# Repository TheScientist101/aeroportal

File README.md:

# Aeroportal

Aeroportal is a weather-centered home hub that is designed with simplicity at its core.

The dashboard is hosted at: https://aeroportal.urjith.dev/

# Features

- Weather information
- Time and date
- Alarms
- Broadcast audio messages

# Hardware

## PCB

The PCB is designed in KiCad which is in the `pcb` folder. The electronics consist of a Wemos C3 mini, a TFT display, an I2S amplifier, and a speaker. The PCB is designed to be powered by a USB-C cable connected a wall outlet.

|         Schematic         |         PCB         |
| :-----------------------: | :-----------------: |
|  |  |

- [x] I ran DRC in KiCad and have made sure there are 0 errors!

## Case

The case is designed in Openscad which is in the `cad` folder. To assemble, print the top and bottom parts of the case and assemble them as shown in `cad/assembled.scad`. Glue the holes in the top part to the bottom part to help keep the case together.

It's supposed to look like a lightning bolt, but it I've squeezed it a little due to sizing constraints.

# Software

## Website

The dashboard website is written in Next.js with the Next UI library for the UI components. The website is in the `website` folder. The website is hosted at: https://aeroportal.urjith.dev/.

## Firmware

The firmware is written in Circuitpython and is currently very rudamentary since I do not currently have the hardware to test it. The firmware is in the `firmware` folder. It _should_ be able to connect to the internet, display the weather information on the TFT display, and play scheduled alarms or broadcasted messages (using the API).

- [x] I remembered to exclude any personal information, including API Keys, WiFi passwords, etc

# BOM

Provided by dari // alex:

- 1x WeMos C3 Mini (as a cheaper replacement for the S2) WITHOUT FEMALE HEADERS
- 1x ST7735 1.8" LCD display WITHOUT FEMALE HEADERS. Male headers soldered!

I will be printing my case myself for the additional $10 in my grant.

- 1x Top Half of the Case
- 1x Bottom Half of the Case

I will be sourcing the following parts with my grant:

- 1x PCB from JLCPCB
  - $2 for 5x + $1.50 shipping
- 1x 2.5 Inch 4 Ohm, 3 Watt Speaker [(AliExpress)](https://www.aliexpress.us/item/2251832660654764.html)
  - $3.69 + $1.99 shipping
- 1x MAX98357A I2S Amplifier [(AliExpress)](https://www.aliexpress.us/item/3256805196806369.html)
  - $1.73
- 1x USB-C Cable [(AliExpress)](https://www.aliexpress.us/item/3256806318726664.html)
  - $3.21
- 1x 18 AWG Wire for Speaker [(AliExpress)](https://www.aliexpress.us/item/3256807019333756.html)
  - $8.66
  - Note, this price has been fluctuating a lot (it was around $5 earlier), so I may use a different link if it goes up too much.

Total before tax: $22.78
Total after tax: $24.66

I'll also be source the following parts myself since I already have them and would like to help Hack Club:

- 1x 10 Ohm Resistor

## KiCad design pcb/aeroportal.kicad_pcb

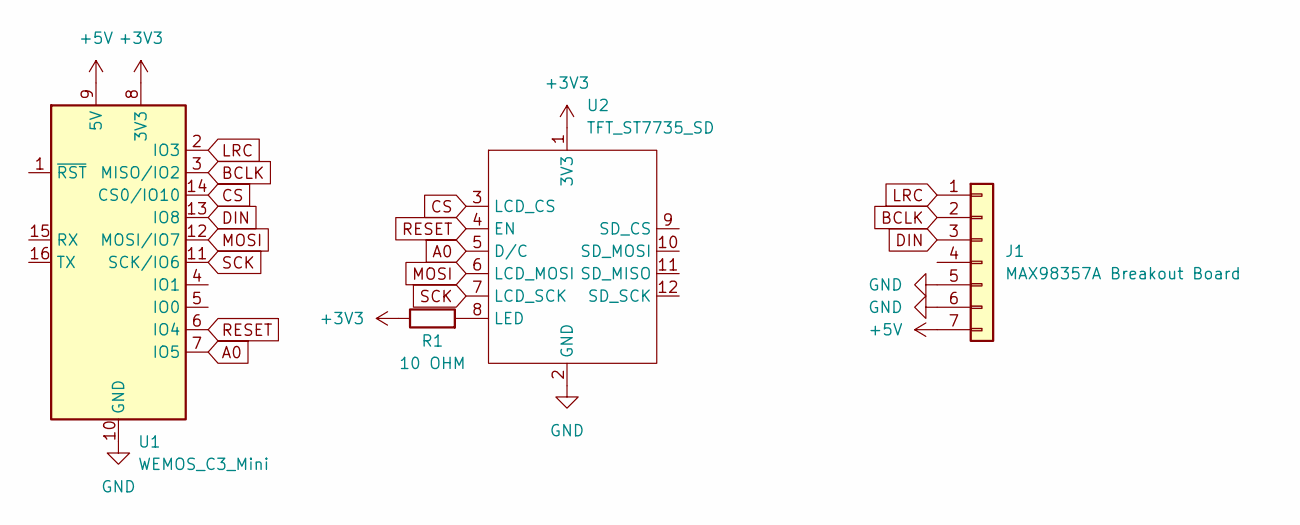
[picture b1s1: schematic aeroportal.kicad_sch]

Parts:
J1: MAX98357A Breakout Board; PinHeader_1x07_P2.54mm_Vertical
R1: 10 OHM; R_Axial_DIN0207_L6.3mm_D2.5mm_P10.16mm_Horizontal
U1: WEMOS_C3_Mini; WEMOS_D1_mini_light
U2: TFT_ST7735_SD

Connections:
+3V3: R1.1, U1.8 (3V3), U2.1 (3V3)
+5V: J1.7, U1.9 (5V)
A0: U1.7 (IO5), U2.5 (D/C)
BCLK: J1.2, U1.3 (MISO/IO2)
CS: U1.14 (CS0/IO10), U2.3 (LCD_CS)
DIN: J1.3, U1.13 (IO8)
GND: J1.5, J1.6, U1.10 (GND), U2.2 (GND)
LRC: J1.1, U1.2 (IO3)
MOSI: U1.12 (MOSI/IO7), U2.6 (LCD_MOSI)
unnamed: R1.2, U2.8 (LED)
RESET: U1.6 (IO4), U2.4 (EN)
SCK: U1.11 (SCK/IO6), U2.7 (LCD_SCK)

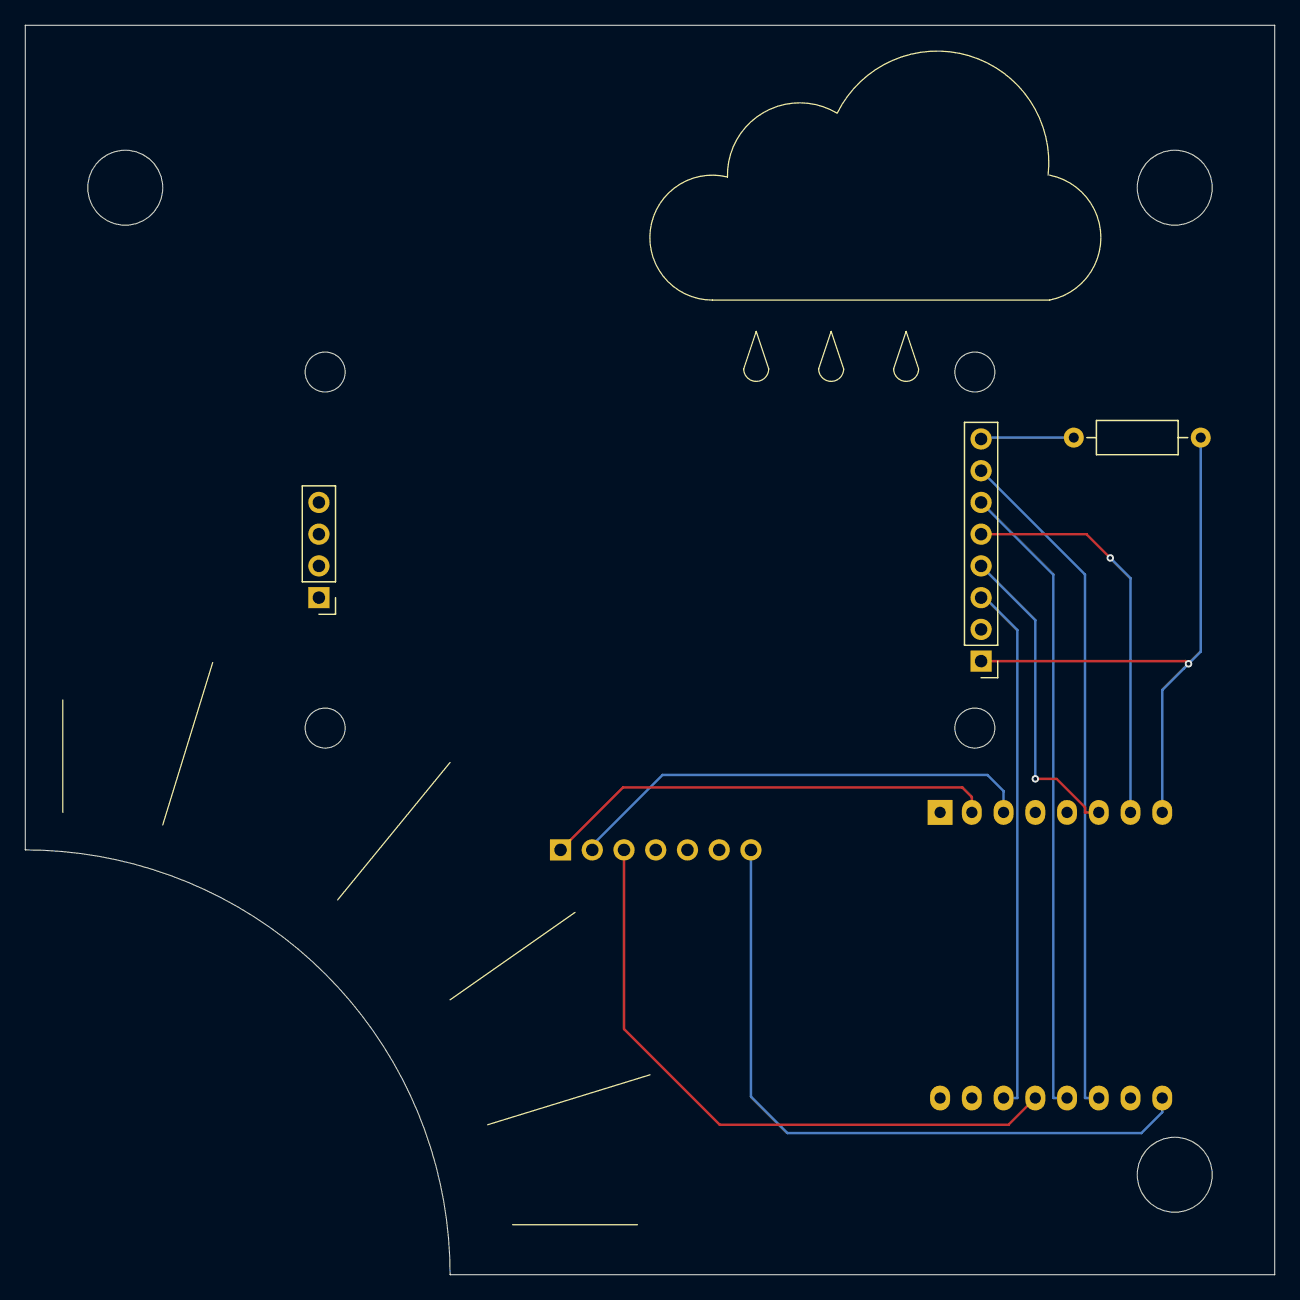
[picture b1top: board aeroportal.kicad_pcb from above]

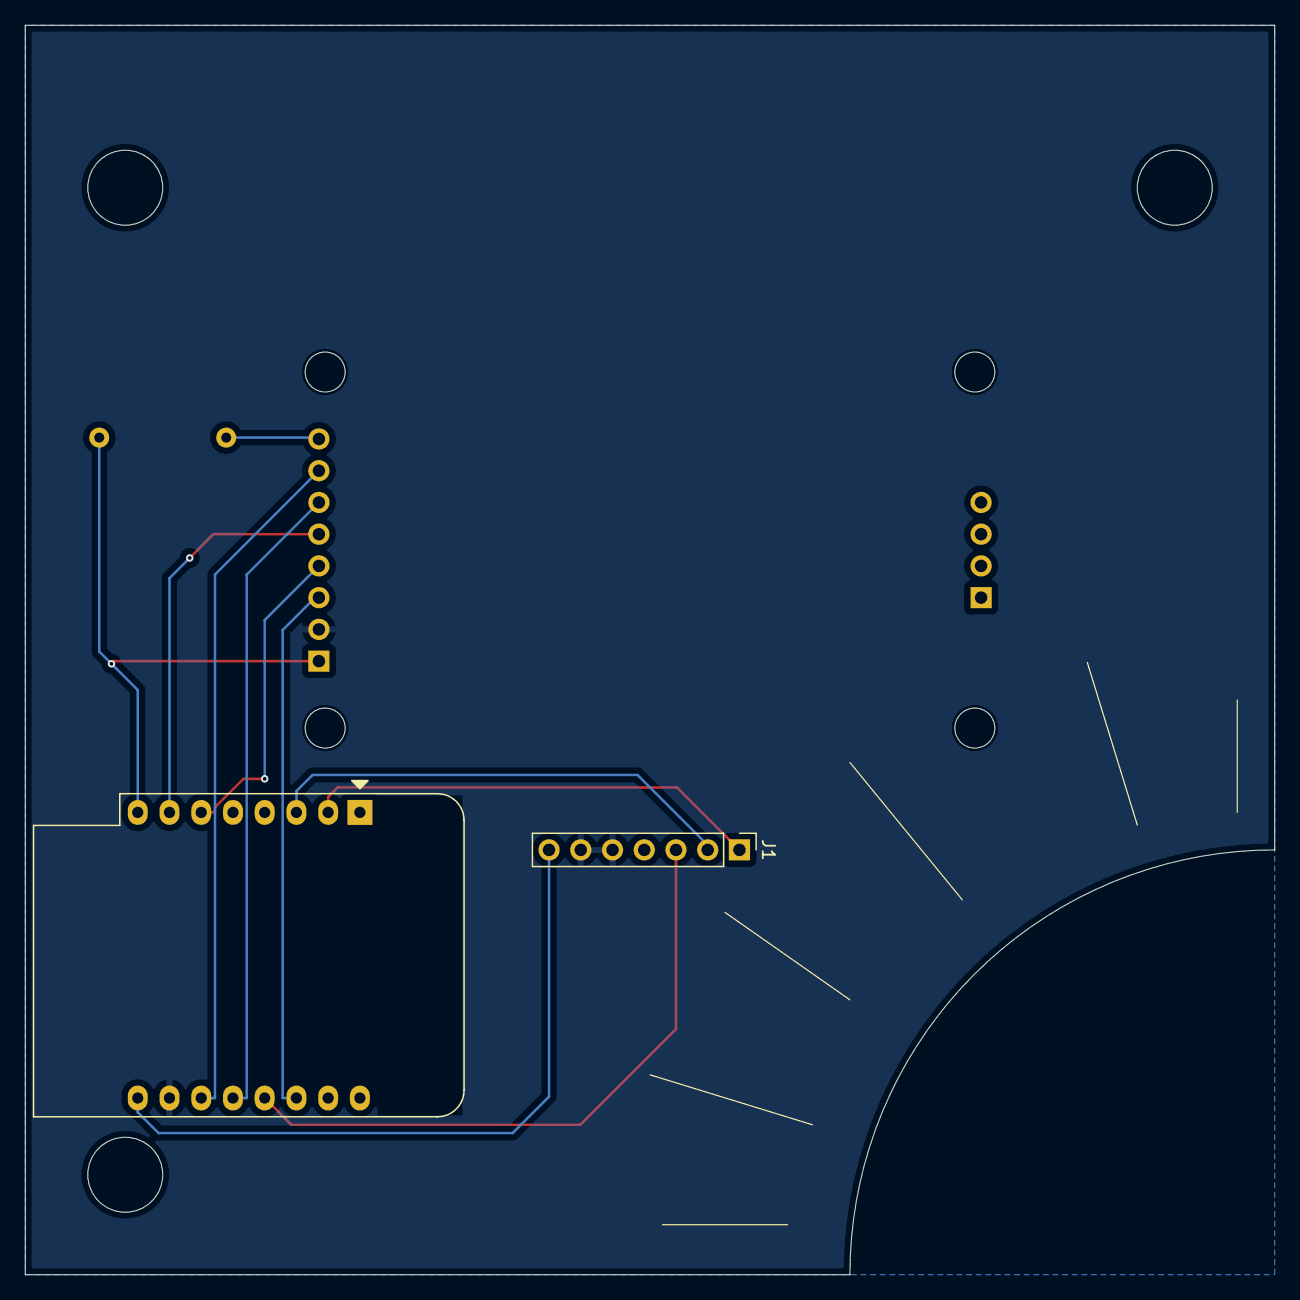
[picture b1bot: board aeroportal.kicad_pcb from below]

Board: 2 copper layers, 100.0 x 100.0 mm, 4 parts (2 on the bottom side), 12 nets.

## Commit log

2024-12-14 Designed schematic and pcb
2024-12-15 Created case (missing usb hole) and enlarged PCB with hole for speaker
2024-12-15 Remove DS Store
2024-12-15 Added USB hole to case
2024-12-15 Add gitignore for kicad
2024-12-15 Remove 0 depth planes in CAD and reroute PCB w/ new LCD model
2024-12-19 Created home page for portal website
2024-12-19 Change to use axios for fetchWeather cause the regular library is silly
2024-12-20 Fixed website build errors
2024-12-20 Versioning untracked files
2024-12-20 Potentially fixing the vercel deployment issue
2024-12-20 Changed favicon of website
2024-12-20 Fixed favicon background to be transparent
2024-12-20 Created basic firmware and fixed unconnected pin for speaker
2024-12-20 Added settings page and get-alarms route for firmware api
2024-12-20 Fixed localstorage build issues
2024-12-20 Added README for whole project and website
2025-01-31 Added pcb and schematic for readme
2025-02-02 Reduced pcb size to 100mm x 100mm to reduce costs
2025-02-02 Made case into lightning bolt shape that is compatible with new smaller pcb
2025-02-02 Added BOM to readme
